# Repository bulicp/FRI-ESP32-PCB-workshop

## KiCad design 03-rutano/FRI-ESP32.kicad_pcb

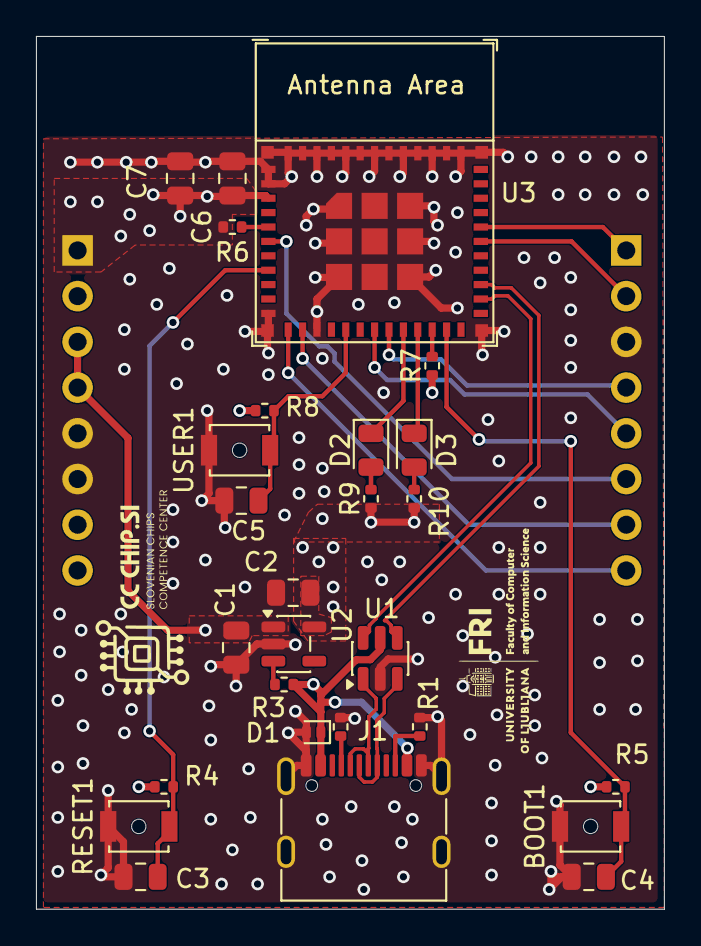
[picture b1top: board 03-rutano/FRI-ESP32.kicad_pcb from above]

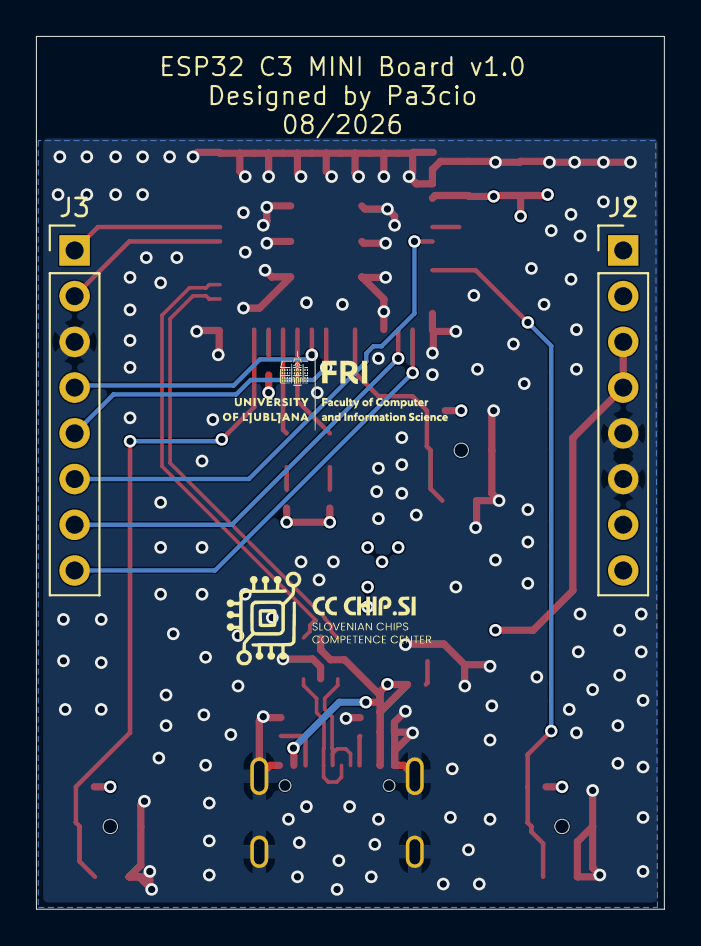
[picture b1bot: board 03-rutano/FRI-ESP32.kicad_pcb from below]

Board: 4 copper layers, 34.9 x 48.5 mm, 31 parts (3 on the bottom side), 26 nets.

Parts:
BOOT1: SW_Push; SW_SPST_B3U-1000P-B
C1, C7: 10uF; C_0805_2012Metric
C2: 4.7uF; C_0805_2012Metric
C3, C4, C5, C6: 100nF; C_0805_2012Metric
CC: LOGO; CCChipSI12x6
CC#2: LOGO; CCChipSI12x6
D1: PESD5V0L1ULD; D_SOD-882D
D2: LED GREEN; LED_0805_2012Metric
D3: LED YELLOW; LED_0805_2012Metric
J1: USB_C_Receptacle_USB2.0_16P; USB_C_Receptacle_G-Switch_GT-USB-7010ASV
J2, J3: Conn_01x08; PinHeader_1x08_P2.54mm_Vertical
R1, R2: 5.1K; R_0402_1005Metric
R3: 4.7K; R_0402_1005Metric
R4, R5, R6, R7, R8: 10K; R_0402_1005Metric
R9, R10: 330R; R_0402_1005Metric
RESET1: SW_Push; SW_SPST_B3U-1000P-B
U1: USBLC6-2SC6; SOT-23-6
U2: XC6220B331MR; SOT-23-5
U3: ESP32-C3-MINI-1
USER1: SW_Push; SW_SPST_B3U-1000P-B

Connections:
+3.3V: C2.1, C6.1, C7.1, J2.1, J2.8, R4.1, R5.1, R6.1, R7.1, R8.1, R9.1, R10.1, U2.5 (VOUT), U3.3 (3V3)
/Power/D+: J1.A6 (D+), J1.B6 (D+), U1.3 (I/O2)
/Power/D-: J1.A7 (D-), J1.B7 (D-), U1.1 (I/O1)
EN: C3.1, R4.2, RESET1.2, U3.8 (EN/CHIP_PU)
GND: BOOT1.1, C1.2, C2.2, C3.2, C4.2, C5.2, C6.2, C7.2, D1.2 (A), J1.A1 (GND), J1.A12 (GND), J1.B1 (GND), J1.B12 (GND), J1.SH (SHIELD), J2.5, J2.6, J3.3, R1.2, R2.2, RESET1.1, U1.2 (GND), U2.2 (GND), U3.1 (GND), U3.2 (GND), U3.11 (GND), U3.14 (GND), U3.36 (GND), U3.37 (GND), U3.38 (GND), U3.39 (GND), U3.40 (GND), U3.41 (GND), U3.42 (GND), U3.43 (GND), U3.44 (GND), U3.45 (GND), U3.46 (GND), U3.47 (GND), U3.48 (GND), U3.49 (GND), U3.50 (GND), U3.51 (GND), U3.52 (GND), U3.53 (GND), USER1.1
GPIO0: J3.8, U3.12 (GPIO0/ADC1_CH0/XTAL_32K_P)
GPIO1: J3.7, U3.13 (GPIO1/ADC1_CH1/XTAL_32K_N)
GPIO2_BOOT: R6.2, U3.5 (GPIO2/ADC1_CH2)
GPIO3: J3.6, U3.6 (GPIO3/ADC1_CH3)
GPIO4: J3.5, U3.18 (GPIO4/ADC1_CH4)
GPIO5: J3.4, U3.19 (GPIO5/ADC2_CH0)
GPIO8_BOOT: R7.2, U3.22 (GPIO8)
GPIO9_BOOT: BOOT1.2, C4.1, R5.2, U3.23 (GPIO9)
LED0: D2.1 (K), U3.20 (GPIO6)
LED1: D3.1 (K), U3.21 (GPIO7)
unnamed: D2.2 (A), R9.2
unnamed: D3.2 (A), R10.2
unnamed: J1.A5 (CC1), R2.1
unnamed: J1.B5 (CC2), R1.1
unnamed: R3.1, U2.3 (CE)
RXD0: J3.2, U3.30 (GPIO20/U0RXD)
TXD0: J3.1, U3.31 (GPIO21/U0TXD)
USB_D+: U1.4 (I/O2), U3.27 (GPIO19/USB_D+)
USB_D-: U1.6 (I/O1), U3.26 (GPIO18/USB_D-)
USER_BTN: C5.1, R8.2, U3.16 (GPIO10), USER1.2
VBUS: C1.1, D1.1 (K), J1.A4 (VBUS), J1.A9 (VBUS), J1.B4 (VBUS), J1.B9 (VBUS), J2.3, J2.4, R3.2, U1.5 (VBUS), U2.1 (VIN)

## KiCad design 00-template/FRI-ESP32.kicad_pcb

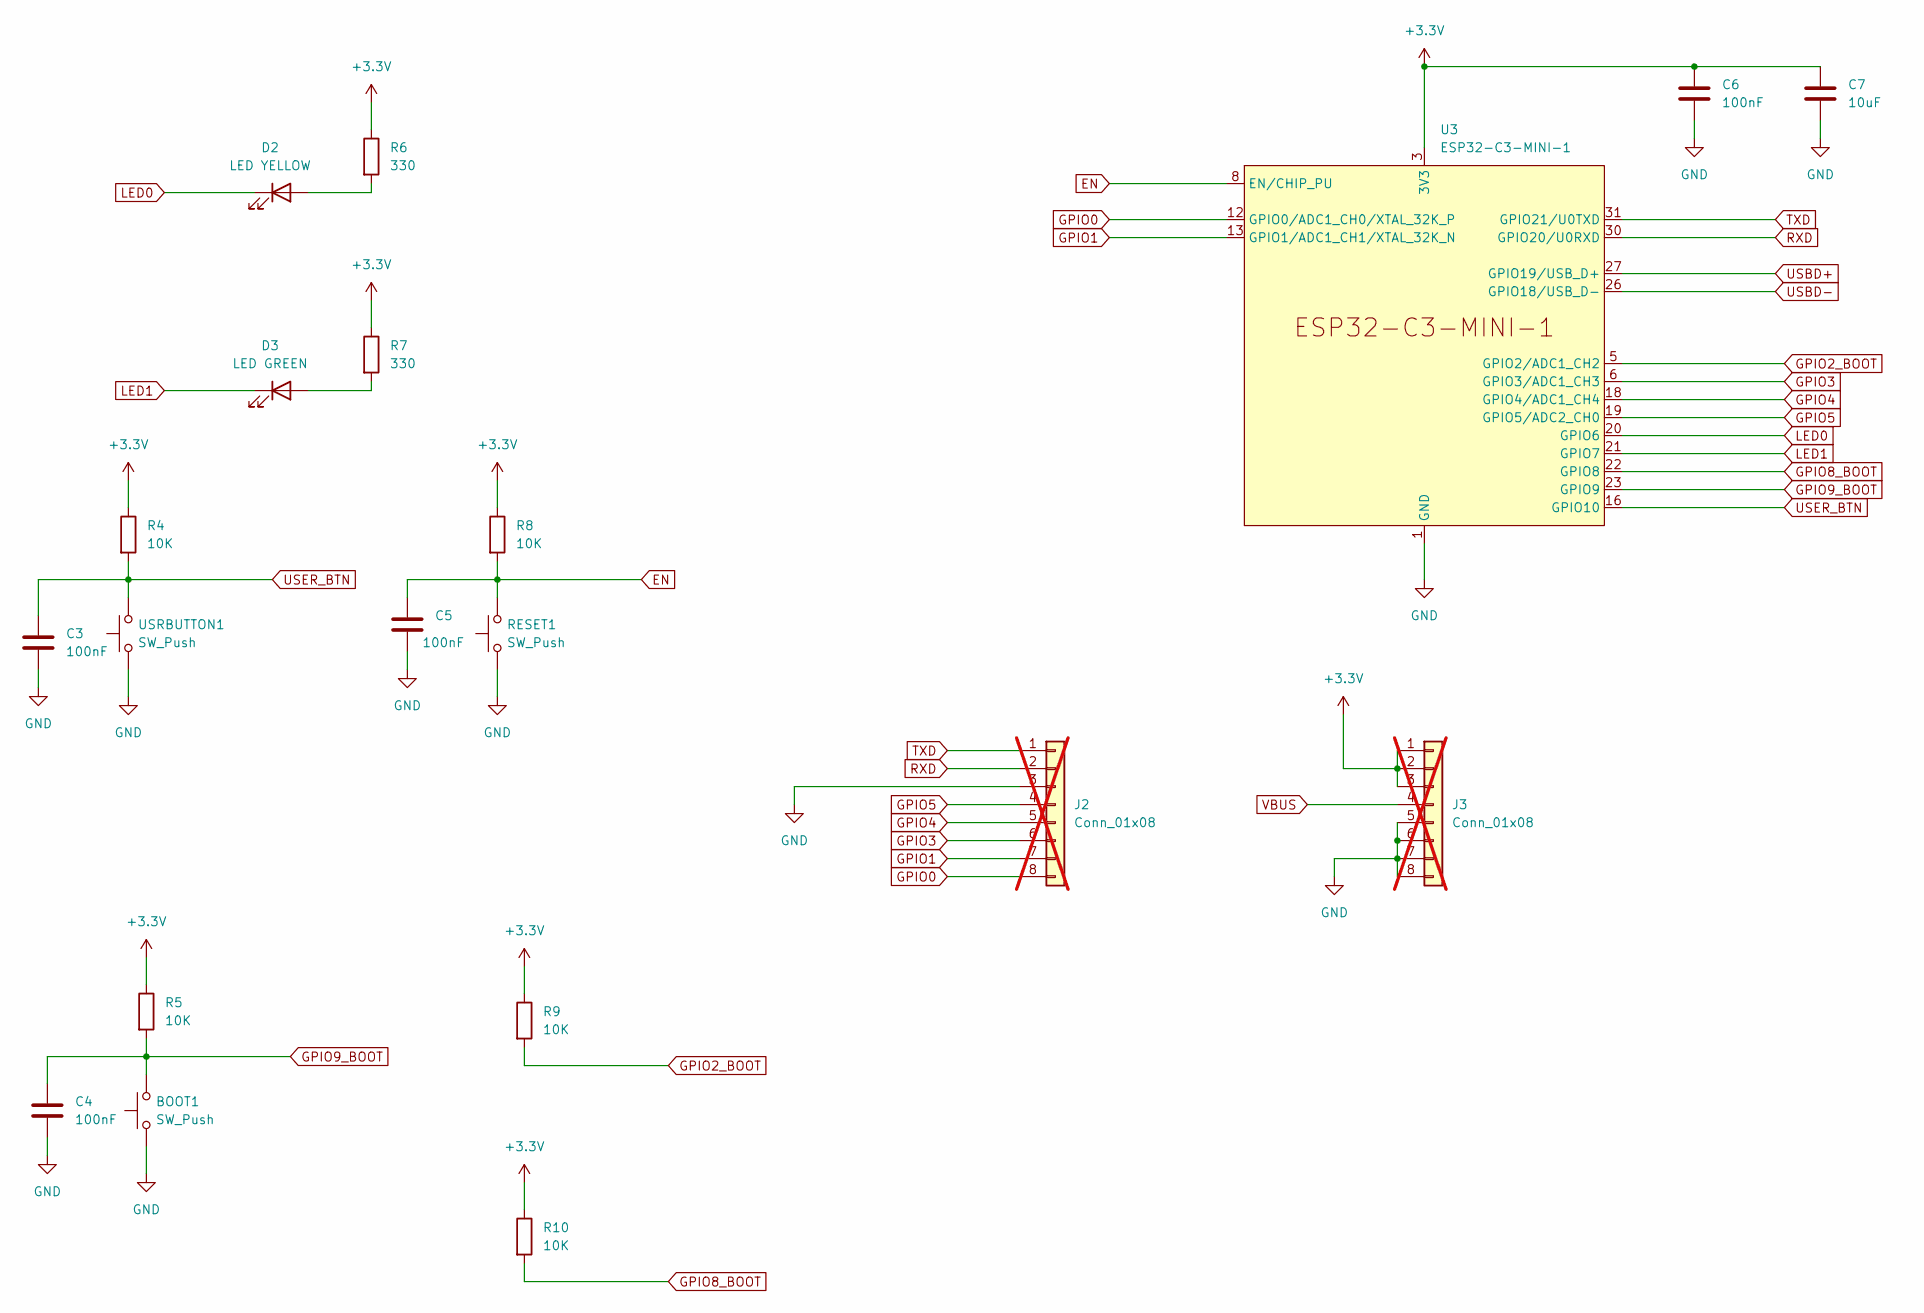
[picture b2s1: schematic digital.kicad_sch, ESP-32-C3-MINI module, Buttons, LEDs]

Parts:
BOOT1: SW_Push; SW_SPST_B3U-1000P-B; MPN B3U-1000P; LCSC C231329
C3, C4, C5, C6: 100nF; C_0402_1005Metric
C7: 10uF; C_0805_2012Metric
D2: LED YELLOW; LED_0805_2012Metric; LCSC C2297
D3: LED GREEN; LED_0805_2012Metric; LCSC C2297
J2, J3: Conn_01x08; PinHeader_1x08_P2.54mm_Vertical; not fitted
R4, R5, R8, R9, R10: 10K; R_0402_1005Metric
R6, R7: 330; R_0402_1005Metric
RESET1: SW_Push; SW_SPST_B3U-1000P-B; MPN B3U-1000P; LCSC C231329
U3: ESP32-C3-MINI-1; MPN ESP32-C3-MINI-1-N4; LCSC C2838502
USRBUTTON1: SW_Push; SW_SPST_B3U-1000P-B; MPN B3U-1000P; LCSC C231329

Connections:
+3.3V: C6.1, C7.1, J3.1, J3.2, J3.3, R4.1, R5.1, R6.1, R7.1, R8.1, R9.1, R10.1, U3.3 (3V3); also elsewhere on the board
EN: C5.1, R8.2, RESET1.2, U3.8 (EN/CHIP_PU)
GND: BOOT1.1, C3.2, C4.2, C5.2, C6.2, C7.2, J2.3, J3.5, J3.6, J3.7, J3.8, RESET1.1, U3.1 (GND), U3.2 (GND), U3.11 (GND), U3.14 (GND), U3.36 (GND), U3.37 (GND), U3.38 (GND), U3.39 (GND), U3.40 (GND), U3.41 (GND), U3.42 (GND), U3.43 (GND), U3.44 (GND), U3.45 (GND), U3.46 (GND), U3.47 (GND), U3.48 (GND), U3.49 (GND), U3.50 (GND), U3.51 (GND), U3.52 (GND), U3.53 (GND), USRBUTTON1.1; also elsewhere on the board
GPIO0: J2.8, U3.12 (GPIO0/ADC1_CH0/XTAL_32K_P)
GPIO1: J2.7, U3.13 (GPIO1/ADC1_CH1/XTAL_32K_N)
GPIO2_BOOT: R9.2, U3.5 (GPIO2/ADC1_CH2)
GPIO3: J2.6, U3.6 (GPIO3/ADC1_CH3)
GPIO4: J2.5, U3.18 (GPIO4/ADC1_CH4)
GPIO5: J2.4, U3.19 (GPIO5/ADC2_CH0)
GPIO8_BOOT: R10.2, U3.22 (GPIO8)
GPIO9_BOOT: BOOT1.2, C4.1, R5.2, U3.23 (GPIO9)
LED0: D2.1 (K), U3.20 (GPIO6)
LED1: D3.1 (K), U3.21 (GPIO7)
unnamed: D2.2 (A), R6.2
unnamed: D3.2 (A), R7.2
RXD: J2.2, U3.30 (GPIO20/U0RXD)
TXD: J2.1, U3.31 (GPIO21/U0TXD)
USBD+: U3.27 (GPIO19/USB_D+); also elsewhere on the board
USBD-: U3.26 (GPIO18/USB_D-); also elsewhere on the board
USER_BTN: C3.1, R4.2, U3.16 (GPIO10), USRBUTTON1.2
VBUS: J3.4; also elsewhere on the board

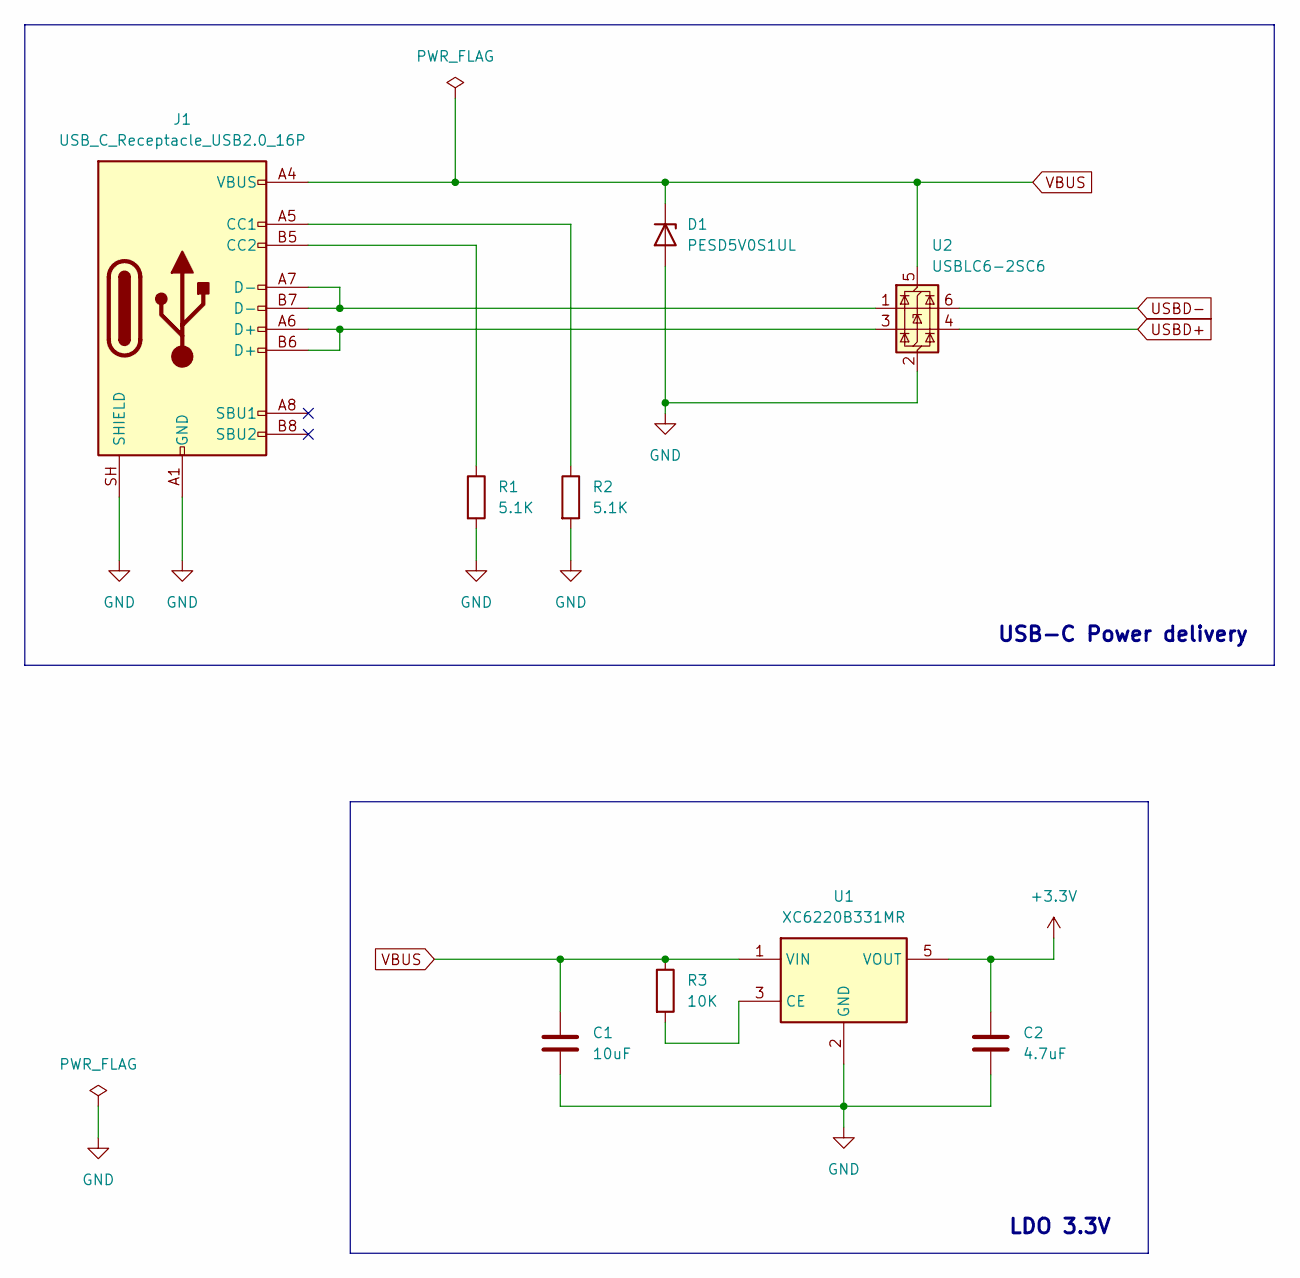
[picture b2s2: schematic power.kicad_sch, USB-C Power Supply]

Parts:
C1: 10uF; C_0805_2012Metric
C2: 4.7uF; C_0805_2012Metric
D1: PESD5V0S1UL; D_SOD-882
J1: USB_C_Receptacle_USB2.0_16P; USB_C_Receptacle_G-Switch_GT-USB-7010ASV; MPN GT-USB-7010ASV; LCSC C2988369
R1, R2: 5.1K; R_0402_1005Metric
R3: 10K; R_0402_1005Metric
U1: XC6220B331MR; SOT-23-5
U2: USBLC6-2SC6; SOT-23-6; LCSC C7519

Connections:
+3.3V: C2.1, U1.5 (VOUT); also elsewhere on the board
GND: C1.2, C2.2, D1.2 (A), J1.A1 (GND), J1.A12 (GND), J1.B1 (GND), J1.B12 (GND), J1.SH (SHIELD), R1.2, R2.2, U1.2 (GND), U2.2 (GND); also elsewhere on the board
unnamed: J1.A5 (CC1), R2.1
unnamed: J1.B5 (CC2), R1.1
unnamed: J1.A6 (D+), J1.B6 (D+), U2.3 (I/O2)
unnamed: J1.A7 (D-), J1.B7 (D-), U2.1 (I/O1)
unnamed: R3.2, U1.3 (CE)
USBD+: U2.4 (I/O2); also elsewhere on the board
USBD-: U2.6 (I/O1); also elsewhere on the board
VBUS: C1.1, D1.1 (K), J1.A4 (VBUS), J1.A9 (VBUS), J1.B4 (VBUS), J1.B9 (VBUS), R3.1, U1.1 (VIN), U2.5 (VBUS); also elsewhere on the board

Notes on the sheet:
LDO 3.3V
USB-C Power delivery

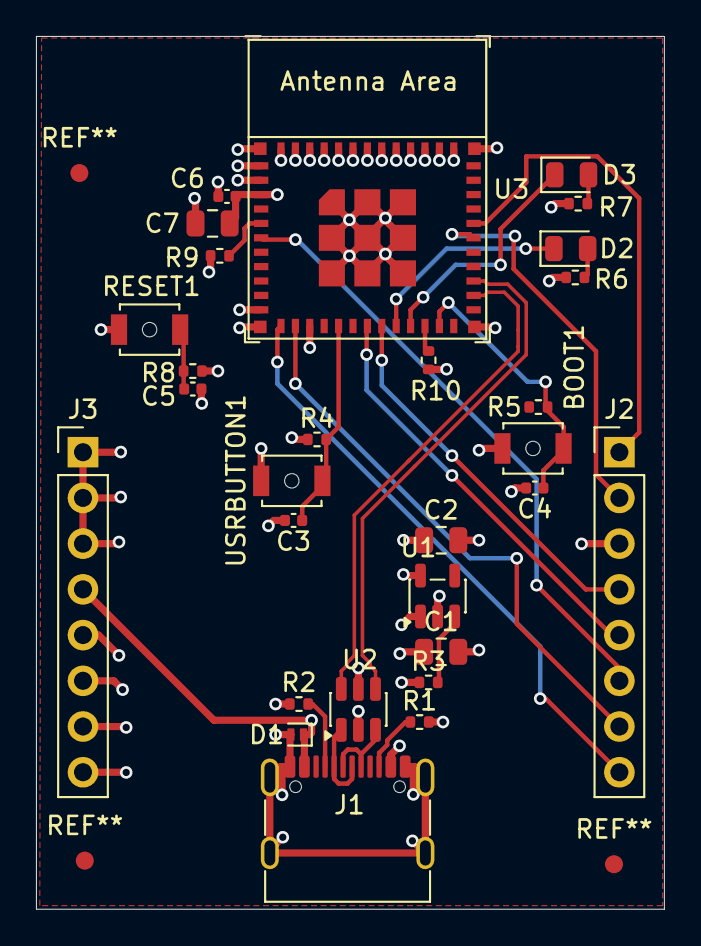
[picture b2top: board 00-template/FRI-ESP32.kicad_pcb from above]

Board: 4 copper layers, 34.9 x 48.5 mm, 29 parts (0 on the bottom side), 26 nets.
